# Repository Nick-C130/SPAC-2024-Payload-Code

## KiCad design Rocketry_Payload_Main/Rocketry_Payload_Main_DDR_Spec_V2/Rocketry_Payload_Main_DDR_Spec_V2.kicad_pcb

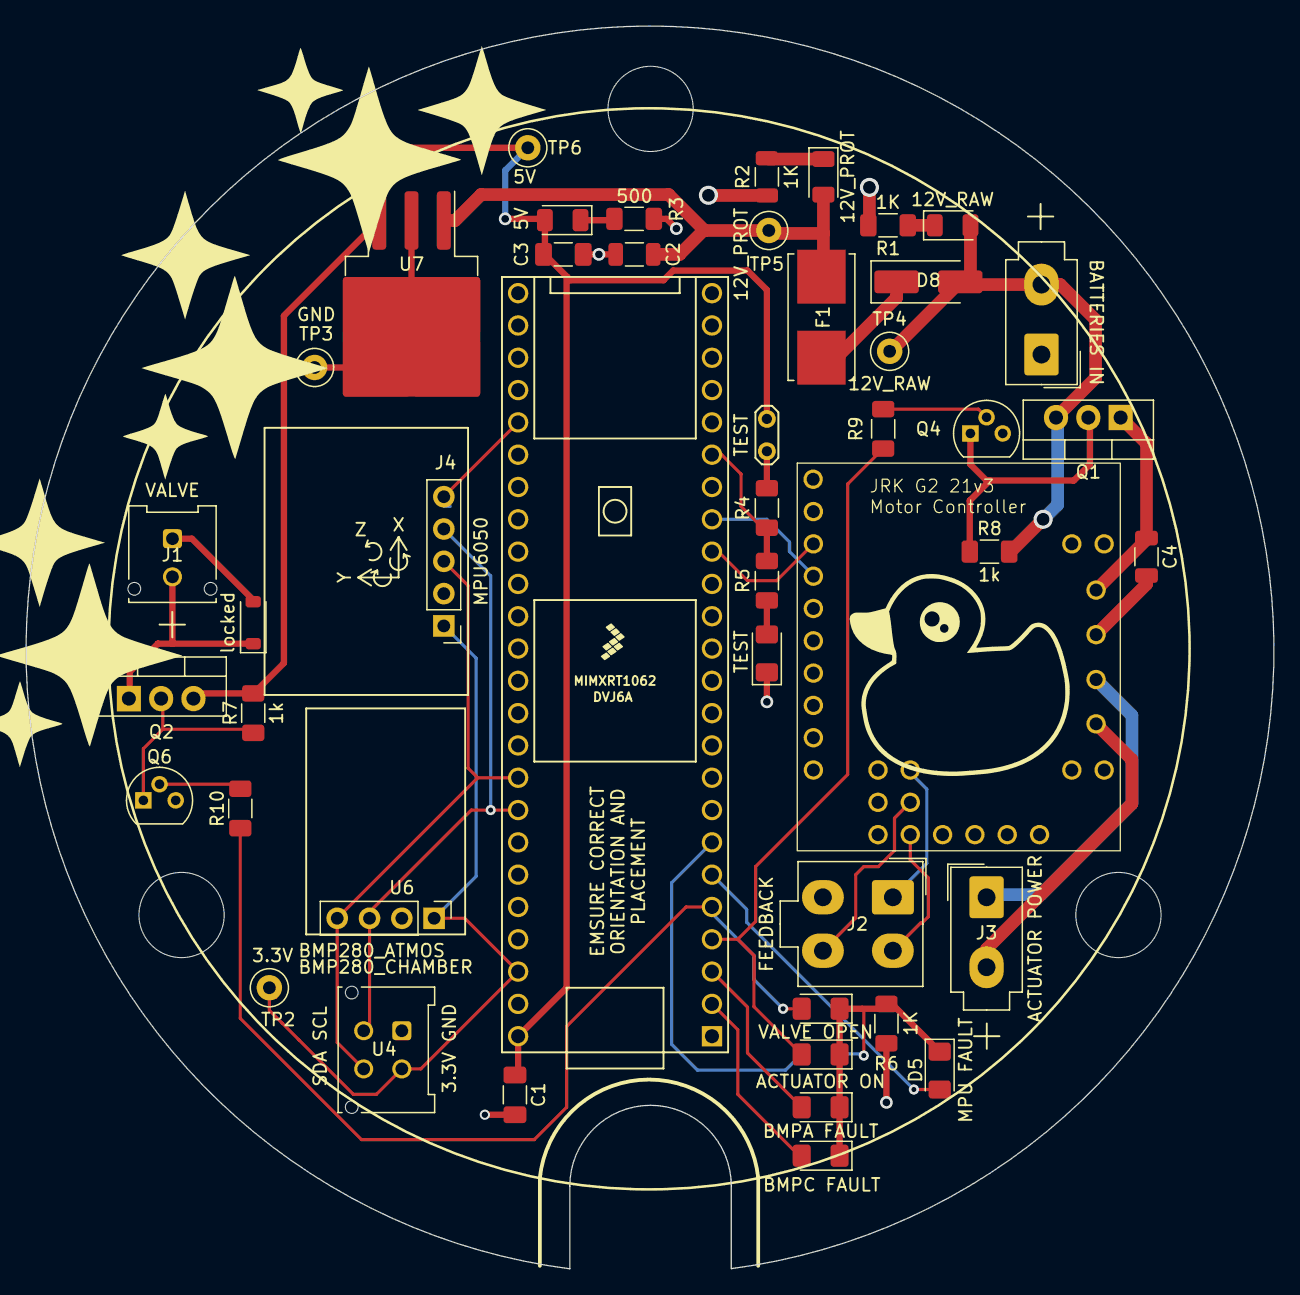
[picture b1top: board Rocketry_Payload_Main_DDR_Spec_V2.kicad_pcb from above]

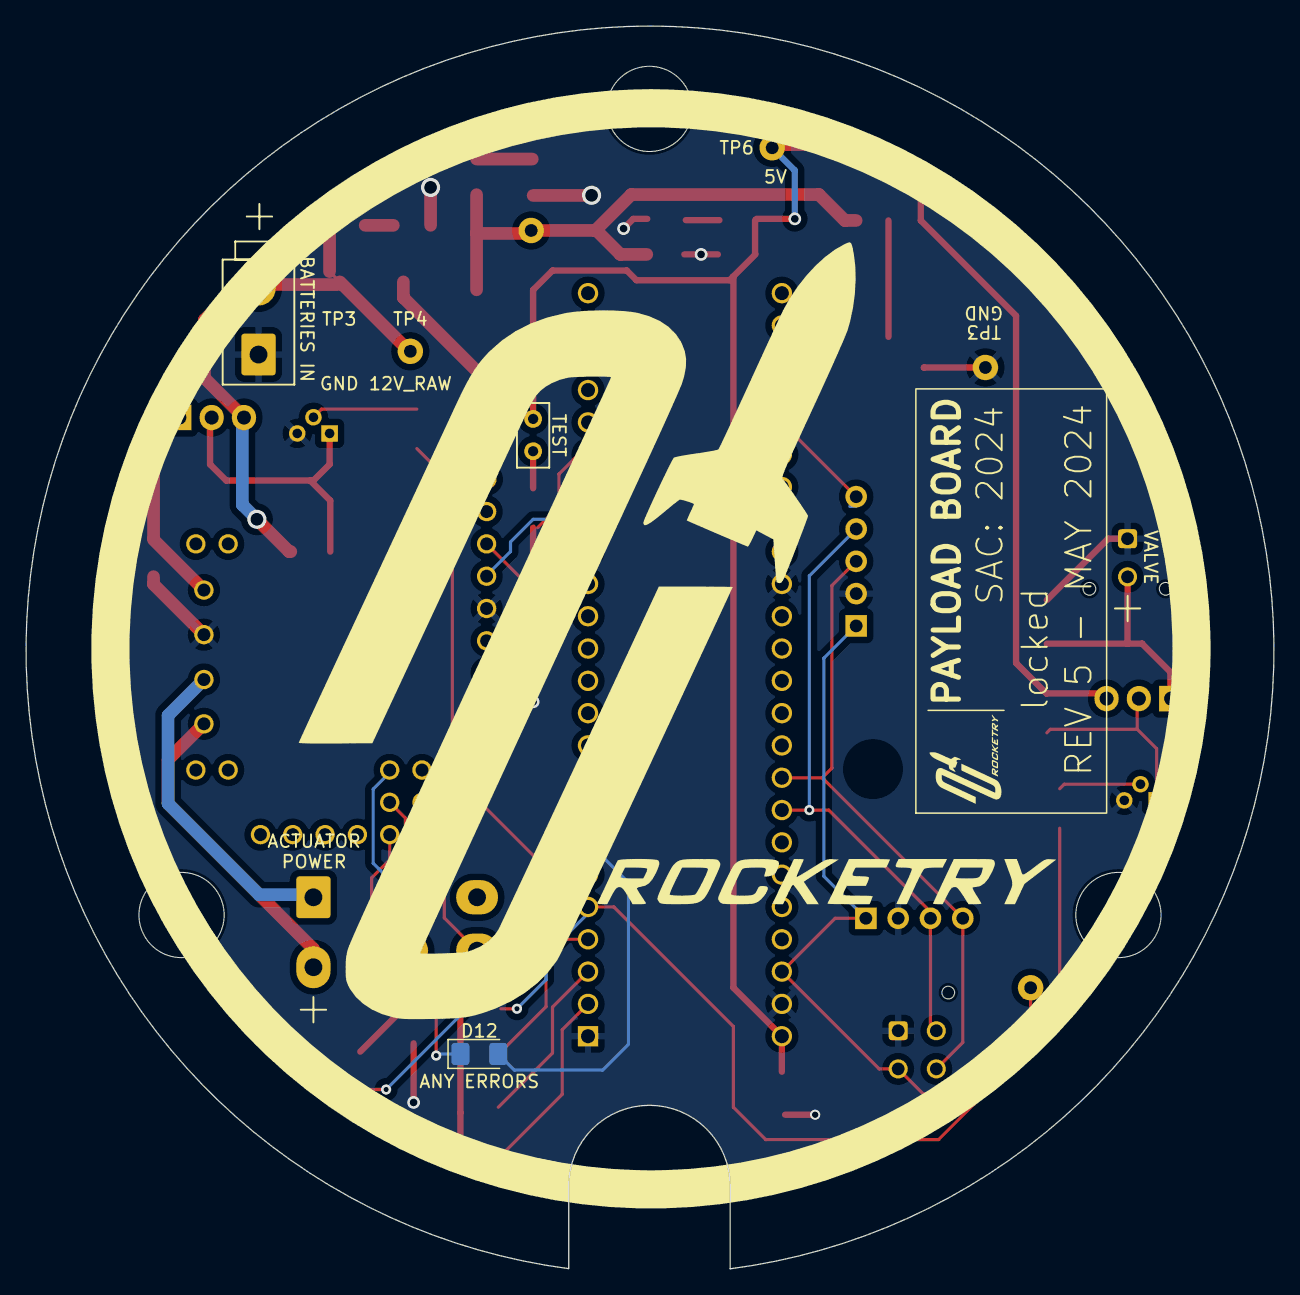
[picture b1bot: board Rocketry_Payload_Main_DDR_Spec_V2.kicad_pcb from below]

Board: 2 copper layers, 98.1 x 97.7 mm, 48 parts (2 on the bottom side), 35 nets.

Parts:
C1: C; C_1206_3216Metric_Pad1.33x1.80mm_HandSolder
C2: 0.1uF; C_1206_3216Metric
C3: 0.1uF; C_1206_3216Metric_Pad1.33x1.80mm_HandSolder
C4: C; C_1206_3216Metric
COMMISIONING_PWR1: BATTERIES IN; Molex_Mini-Fit_Jr_5566-02A_2x01_P4.20mm_Vertical
D1: BMPC FAULT; D_1206_3216Metric_Pad1.42x1.75mm_HandSolder
D2: BMPA FAULT; D_1206_3216Metric_Pad1.42x1.75mm_HandSolder
D3: ACTUATOR ON; D_1206_3216Metric_Pad1.42x1.75mm_HandSolder
D4: VALVE OPEN; D_1206_3216Metric_Pad1.42x1.75mm_HandSolder
D5: MPU FAULT; D_1206_3216Metric_Pad1.42x1.75mm_HandSolder
D6: TEST; D_1206_3216Metric_Pad1.42x1.75mm_HandSolder
D7: 12V_RAW; LED_1206_3216Metric
D8: TWGMC-SS34; D_SMA_Handsoldering
D9: 12V_PROT; LED_1206_3216Metric
D10: 5V; LED_1206_3216Metric
D12: ANY ERRORS; D_1206_3216Metric_Pad1.42x1.75mm_HandSolder
F1: SMDFuse; Fuseholder_Littelfuse_Nano2_154x
J1: VALVE; Molex_Micro-Fit_3.0_43045-0212_2x01_P3.00mm_Vertical
J2: FEEDBACK; Molex_Mini-Fit_Jr_5566-04A_2x02_P4.20mm_Vertical
J3: ACTUATOR POWER; Molex_Mini-Fit_Jr_5566-02A_2x01_P4.20mm_Vertical
J4: MPU6050; PinHeader_1x05_P2.54mm_Vertical
Q1, Q2: PMOS; TO-220-3_Vertical
Q4, Q6: NPN; TO-92
R1, R6: 1K; R_1206_3216Metric_Pad1.30x1.75mm_HandSolder
R2: 1K; R_1206_3216Metric
R3: 500; R_1206_3216Metric_Pad1.30x1.75mm_HandSolder
R4, R7, R8: 1k; R_1206_3216Metric_Pad1.30x1.75mm_HandSolder
R5: 1.5k; R_1206_3216Metric_Pad1.30x1.75mm_HandSolder
R9, R10: R; R_1206_3216Metric_Pad1.30x1.75mm_HandSolder
SJ2: TEST; TestPoint_2Pads_Pitch2.54mm_Drill0.8mm
TP2: 3V; TestPoint_Loop_D1.80mm_Drill1.0mm_Beaded
TP3: GND; TestPoint_Loop_D1.80mm_Drill1.0mm_Beaded
TP4: 12V_RAW; TestPoint_Loop_D1.80mm_Drill1.0mm_Beaded
TP5: 12V_PROT; TestPoint_Loop_D1.80mm_Drill1.0mm_Beaded
TP6: 5V; TestPoint_Loop_D1.80mm_Drill1.0mm_Beaded
U2: Teensy4.1; Teensy41
U3: Branding_Block_Rocketry; BRANDING_ROCKETRY
U4: BMP280_CHAMBER; microfit-2x02
U5: Motor_Controller; JRK21V3
U6: BMP280_ATMOS; PinHeader_1x04_P2.54mm_Vertical
U7: LM7805_TO220; TO-263-3_TabPin2
locked: D; D_SOD-123

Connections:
5V: C1.1, C3.1, D10.2 (A), Q2.3 (S), R7.2, SJ2.2, TP6.1, U2.48 (VIN), U7.3 (VO)
12V_PROT: C2.1, D9.2 (A), F1.2, TP5.1, U7.1 (VI)
12V_RAW: COMMISIONING_PWR1.2, D7.2 (A), D8.2 (A), Q1.3 (S), R8.2, TP4.1
/0: D1.2 (A), U2.2 (0_RX1_CRX2_CS1)
/1: D2.2 (A), U2.3 (1_TX1_CTX2_MISO1)
/2: D3.2 (A), R9.2, U2.4 (2_OUT2)
/3: D4.2 (A), R10.1, U2.5 (3_LRCLK2)
/3.3V: J4.1, TP2.1, U2.46 (3V3), U4.2 (Vin_2-6V), U6.5 (Vin_2-6V)
/4: D5.2 (A), U2.6 (4_BCLK2)
/5: D12.2 (A), U2.7 (5_IN2)
/INT: J4.5, U2.29 (37_CS)
/SCK/SCL: J4.4, U2.41 (19_A5_SCL), U4.3 (SCL), U6.3 (SCL)
/SCL2: U2.16 (24_A10_TX6_SCL2), U5.3 (SCL)
/SDA2: U2.17 (25_A11_RX6_SDA2), U5.4 (SDA/AN)
/SDI/SDA: J4.3, U2.40 (18_A4_SDA), U4.4 (SDA), U6.4 (SDA)
/Test_Pin: R4.2, R5.1, U2.19 (27_A13_SCK1)
GND: C1.2, C2.2, C3.2, C4.2, COMMISIONING_PWR1.1, D6.1 (K), J1.1, J4.2, Q4.3 (E), Q6.3 (E), R1.2, R2.2, R3.2, R6.2, TP3.1, U2.1 (GND), U2.34 (GND), U2.47 (GND), U4.1 (GND), U5.5 (GND), U5.10 (GND), U5.26 (GND), U6.1 (GND), U7.2 (GND), locked.2 (A)
Motor: C4.1, Q1.1 (D), U5.25 (VIN)
unnamed: D1.1 (K), D2.1 (K), D3.1 (K), D4.1 (K), D5.1 (K), D12.1 (K), R6.1
unnamed: D6.2 (A), R5.2
unnamed: D7.1 (K), R1.1
unnamed: D8.1 (K), F1.1
unnamed: D9.1 (K), R2.1
unnamed: D10.1 (K), R3.1
unnamed: J2.1, U5.11 (GND)
unnamed: J3.1, U5.27 (OUTA)
unnamed: J3.2, U5.28 (OUTB)
unnamed: Q1.2 (G), Q4.1 (C), R8.1
unnamed: Q2.2 (G), Q6.1 (C), R7.1
unnamed: Q4.2 (B), R9.1
unnamed: Q6.2 (B), R10.2
unnamed: R4.1, SJ2.1
unnamed: J2.4, U5.18 (AUX)
unnamed: J2.2, U5.20 (FBA)
Valve: J1.2, Q2.1 (D), locked.1 (K)

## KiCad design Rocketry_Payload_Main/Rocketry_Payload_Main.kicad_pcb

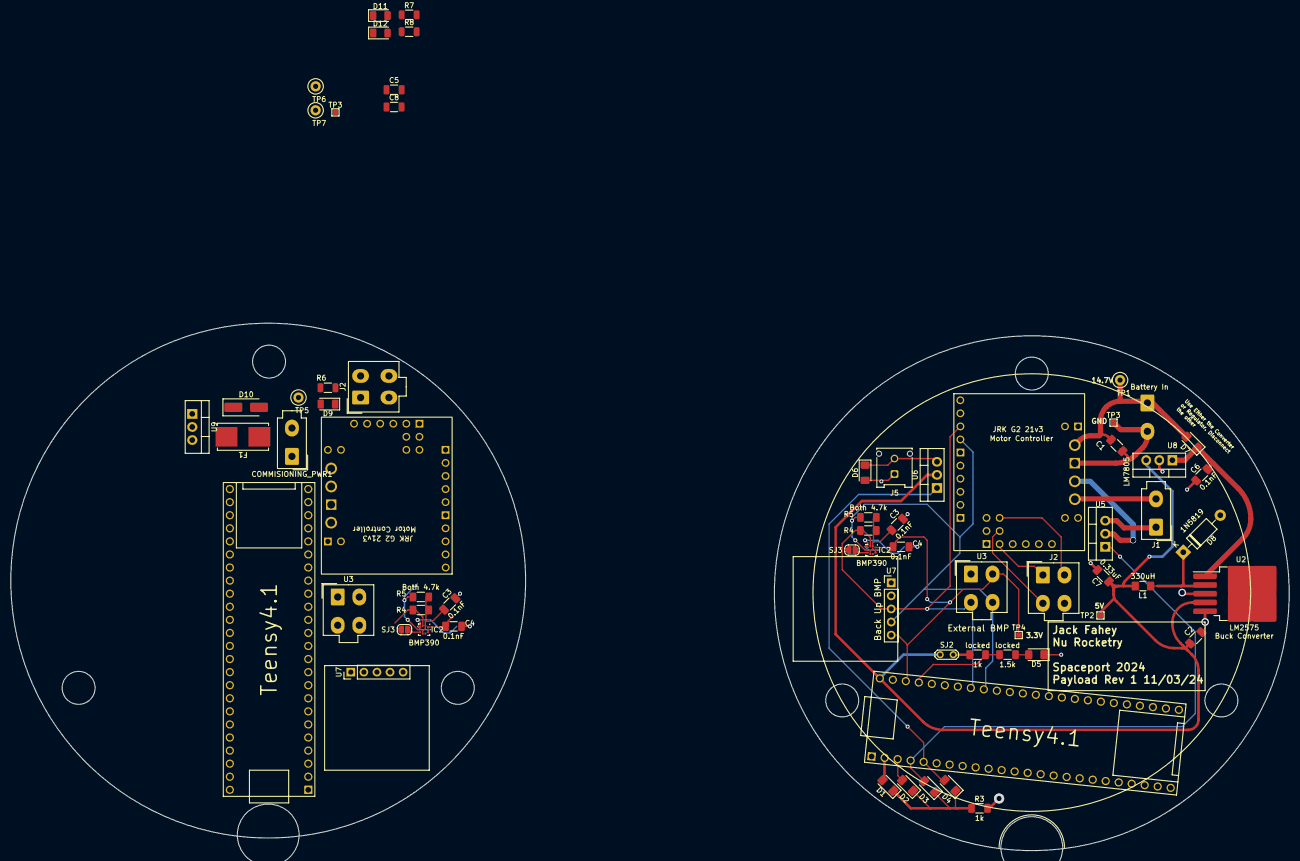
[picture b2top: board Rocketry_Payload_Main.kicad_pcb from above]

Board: 2 copper layers, 248.3 x 102.4 mm, 66 parts (1 on the bottom side), 32 nets.

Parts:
C1, C2: C; C_1206_3216Metric_Pad1.33x1.80mm_HandSolder
C3, C3#2, C4, C4#2: 0.1nF; C_1206_3216Metric_Pad1.33x1.80mm_HandSolder
C5, C8: 0.1uF; C_1206_3216Metric
C6: 100 uF; C_1206_3216Metric_Pad1.33x1.80mm_HandSolder
C7: 330 uF; C_1206_3216Metric_Pad1.33x1.80mm_HandSolder
COMMISIONING_PWR1: COMMISIONING_PWR; Molex_Mini-Fit_Jr_5566-02A_2x01_P4.20mm_Vertical
D1, D2, D5: LED; D_1206_3216Metric_Pad1.42x1.75mm_HandSolder
D3: Motor; D_1206_3216Metric_Pad1.42x1.75mm_HandSolder
D4: Valve; D_1206_3216Metric_Pad1.42x1.75mm_HandSolder
D6, D7: D; D_1206_3216Metric_Pad1.42x1.75mm_HandSolder
D8: 1N5819; D_DO-41_SOD81_P10.16mm_Horizontal
D9: 12V_RAW; LED_1206_3216Metric
D10: TWGMC-SS34; D_SMA_Handsoldering
D11: 12V_PROT; LED_1206_3216Metric
D12: 5V; LED_1206_3216Metric
F1: SMDFuse; Fuseholder_Littelfuse_Nano2_154x
IC2, IC2#2: BMP390; ST_HLGA-10_2x2mm_P0.5mm_LayoutBorder3x2y
J1: Actuators; Molex_Mini-Fit_Jr_5566-02A_2x01_P4.20mm_Vertical
J2, J2#2: Feedback; Molex_Mini-Fit_Jr_5566-04A_2x02_P4.20mm_Vertical
J5: Solenoid; Molex_Micro-Fit_3.0_43045-0212_2x01_P3.00mm_Vertical
J6: Battery In; Molex_Mini-Fit_Jr_5566-02A_2x01_P4.20mm_Vertical
L1: 330 uH; L_1206_3216Metric_Pad1.42x1.75mm_HandSolder
R3: 1K; R_1206_3216Metric_Pad1.30x1.75mm_HandSolder
R4, R4#2, R5, R5#2: 4.7k; R_1206_3216Metric_Pad1.30x1.75mm_HandSolder
R6, R7: 1K; R_1206_3216Metric
R8: 500; R_1206_3216Metric
SJ2: SOLDERJUMPER; TestPoint_2Pads_Pitch2.54mm_Drill0.8mm
SJ3, SJ3#2: SOLDERJUMPER; SolderJumper-2_P1.3mm_Open_RoundedPad1.0x1.5mm
TP1: 12V TestPoint; TestPoint_Loop_D1.80mm_Drill1.0mm_Beaded
TP2: 5V TestPoint; TestPoint_Pad_1.0x1.0mm
TP3, TP3#2: GND TestPoint; TestPoint_Pad_1.0x1.0mm
TP4: 3V TestPoint; TestPoint_Pad_1.0x1.0mm
TP5: 12V_RAW; TestPoint_Loop_D1.80mm_Drill1.0mm_Beaded
TP6: 12V_PROT; TestPoint_Loop_D1.80mm_Drill1.0mm_Beaded
TP7: 5V; TestPoint_Loop_D1.80mm_Drill1.0mm_Beaded
U1, U1#2: Teensy4.1; Teensy41
U2: Buck Converter; TO-263-5_TabPin3
U3, U3#2: BMP280_2; Molex_Mini-Fit_Jr_5566-04A_2x02_P4.20mm_Vertical
U4, U4#2: Motor_Controller; JRK21V3
U5: Mosfet Motor; TO-220-3_Vertical
U6: Valve Mosfet; TO-220-3_Vertical
U7, U7#2: BMP280_Backup; PinHeader_1x05_P2.54mm_Vertical
U8, U9: LM7805_TO220; TO-220-3_Vertical
locked: 1.5k; R_1206_3216Metric_Pad1.30x1.75mm_HandSolder
locked#2: 1k; R_1206_3216Metric_Pad1.30x1.75mm_HandSolder

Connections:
5V: C2.1, C8.1, D12.2 (A), SJ2.2, TP2.1, TP7.1, U1.48 (VIN), U6.2 (Source), U9.3 (VO)
12V_PROT: C5.1, D11.2 (A), F1.2, TP6.1, U9.1 (VI)
12V_RAW: COMMISIONING_PWR1.2, D9.2 (A), D10.2 (A), TP5.1
+5V: C7.1, L1.2, U2.4 (FEEDBACK), U8.3 (VO)
/0: D1.2 (A), U1.2 (0_RX1_CRX2_CS1)
/1: D2.2 (A), U1.3 (1_TX1_CTX2_MISO1)
/2: D3.2 (A), U1.4 (2_OUT2), U5.1 (Gate)
/3: D4.2 (A), U1.5 (3_LRCLK2), U6.1 (Gate)
/3.3V: C4.1, C4#2.1, IC2.10 (VDD), IC2#2.10 (VDD), TP4.1, U1.46 (3V3), U3.2 (Vin_2-6V), U7.2 (Vin_2-6V), U7#2.2 (Vin_2-6V)
/12V PROTECTED: C6.1, D7.1 (K), U2.1 (Vin), U8.1 (VI)
/12V RAW: C1.1, D7.2 (A), J6.1, TP1.1, U4#2.25 (VIN)
/SCK/SCL: IC2.2 (SCK), IC2#2.2 (SCK), R4.1, R4#2.1, U1.41 (19_A5_SCL), U3.3 (SCL), U4#2.3 (SCL), U7.3 (SCL), U7#2.3 (SCL)
/SDI/SDA: IC2.4 (SDI), IC2#2.4 (SDI), R5.1, R5#2.1, U1.40 (18_A4_SDA), U3.4 (SDA), U4#2.4 (SDA/AN), U7.4 (SDA), U7#2.4 (SDA)
/VDDIO: C3.2, C3#2.2, IC2.1 (VDDIO), IC2.6 (CSB), IC2#2.1 (VDDIO), IC2#2.6 (CSB), R4.2, R4#2.2, R5.2, R5#2.2
GND: C1.2, C2.2, C3.1, C3#2.1, C4.2, C4#2.2, C5.2, C6.2, C7.2, C8.2, COMMISIONING_PWR1.1, D5.1 (K), D6.2 (A), D8.2 (A), IC2.3 (Vss), IC2.8 (Vss), IC2.9 (Vss), IC2#2.3 (Vss), IC2#2.8 (Vss), IC2#2.9 (Vss), J5.1, J6.2, R3.2, R6.2, R7.2, R8.2, SJ3.2, SJ3#2.2, TP3.1, U1.1 (GND), U1.34 (GND), U1.47 (GND), U2.3 (GND), U2.5 (ON/OFF), U3.1 (GND), U4#2.5 (GND), U4#2.10 (GND), U4#2.26 (GND), U7.1 (GND), U7#2.1 (GND), U8.2 (GND), U9.2 (GND)
unnamed: D1.1 (K), D2.1 (K), D3.1 (K), D4.1 (K), R3.1
unnamed: D5.2 (A), locked.2
unnamed: D6.1 (K), J5.2, U6.3 (Drain)
unnamed: D8.1 (K), L1.1, U2.2 (Output)
unnamed: D9.1 (K), R6.1
unnamed: D10.1 (K), F1.1
unnamed: D11.1 (K), R7.1
unnamed: D12.1 (K), R8.1
unnamed: IC2.5 (SDO), IC2#2.5 (SDO), SJ3.1, SJ3#2.1
unnamed: J1.1, U5.3 (Drain)
unnamed: J1.2, U4#2.28 (OUTB)
unnamed: SJ2.1, locked#2.1
unnamed: U1.45 (23_A9_CRX1_MCLK1), locked.1, locked#2.2
unnamed: J2.3, U4#2.18 (AUX)
unnamed: J2.2, U4#2.20 (FBA)
unnamed: U4#2.27 (OUTA), U5.2 (Source)
unnamed: J2.1, U4#2.12 (POT)

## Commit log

2024-04-18 Inital Code
    Basic testing
2024-04-18 PID Autotune
    Started cleanup, added autotune, about to clean house
2024-04-18 V6
    Did shit, cleaned up, made mess, cleaned up, added autotune
2024-04-18 Removed extra files
2024-04-23 Final code before launch
2024-05-01 Started adding SITL
    C should be ready, no testing, python has barely started
2024-05-01 Where-I'm-At
2024-05-02 SITL Tests
    For some reason the python script wont start the test, but if you open serial monitor, run the TF command. then close the monitor and run the python script... it should work
    The test data is being sent accuratly and recieved accuratly i belive
2024-05-02 Updated sim to hit 10k
2024-05-02 Updated a few minor things
2024-05-07 KiCAD
2024-05-08 PCB, code equation edit
2024-05-14 Fixed AS also running a test on the actuator
    Bug where AS would go to position then back.
2024-05-14 Fixed same issue in different place
2024-05-16 New LED
2024-05-16 Manual branch merge
2024-05-22 New PID for pressure
2024-05-23 Updated code
2024-05-30 Moved to a velocity controller and VScode with PIO
2024-05-30 Think i have nicer code setup now
    Needs testing still but it does compile
2024-05-31 Niceness updateing
2024-06-01 Moved JRK library to the lib folder
2024-06-01 PID save
    Saves PID struct to eeprom 0 with checksum
2024-06-01 Fixed PID autotunner
    Moved to local library with minor changes
2024-06-01 Added speed limits
2024-06-01 Working
    PID kinda works, wont go negative, tunned half decently, the leak is a nice rate to handle
2024-06-02 Moved sim into C
    Sim works, systems seem to work, need to add inversion for MPU if its upside down
2024-06-10 Flash chip working
2024-06-16 Final code for SPAC2024
2024-10-17 Boiler plate + Matlab transfer
2024-10-20 Serial
